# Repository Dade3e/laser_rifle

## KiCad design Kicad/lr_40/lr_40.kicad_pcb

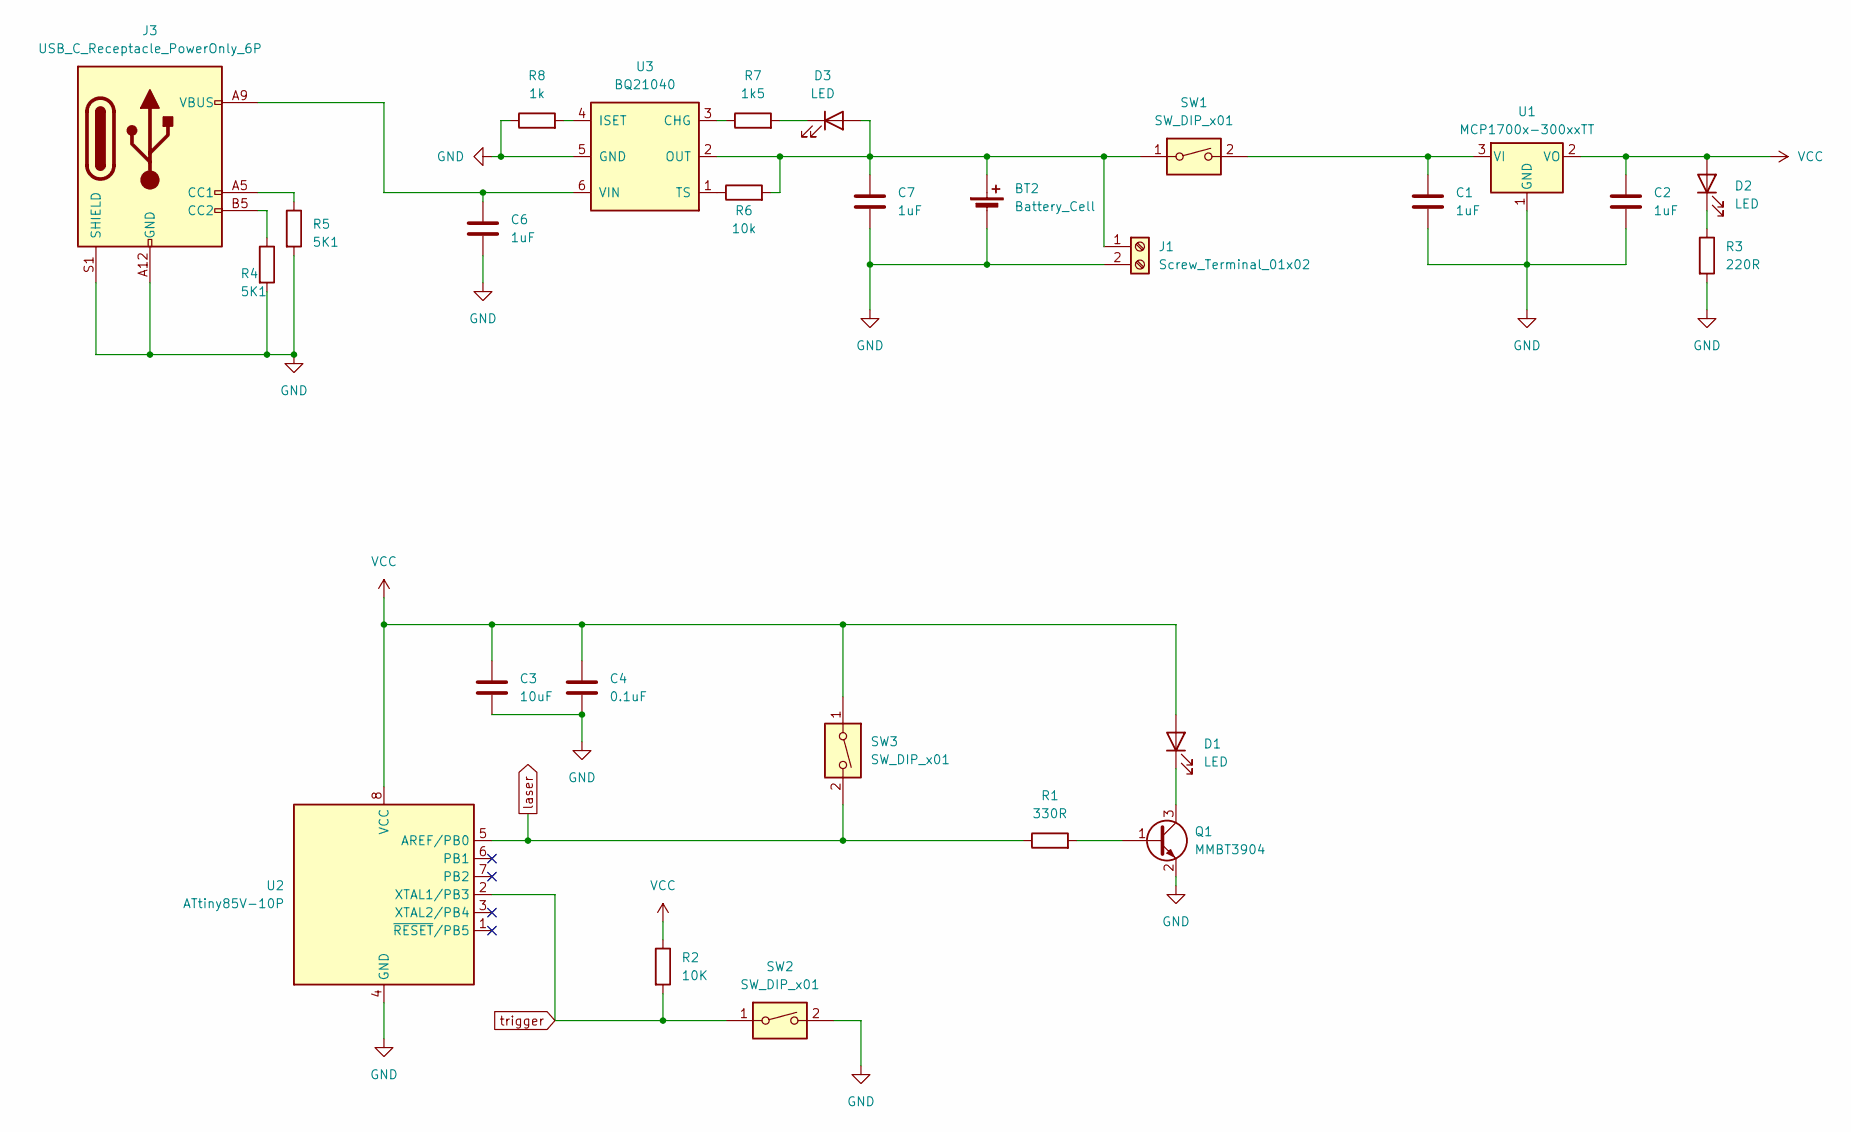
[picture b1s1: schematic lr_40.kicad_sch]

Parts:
BT2: Battery_Cell; Hirose_DF13C_CL535-0402-2-51_1x02-1MP_P1.25mm_Vertical
C1, C2, C6, C7: 1uF; C_0603_1608Metric
C3: 10uF; R_0603_1608Metric
C4: 0.1uF; R_0603_1608Metric
D1: LED; PinSocket_1x02_P2.54mm_Vertical
D2, D3: LED; LED_0603_1608Metric
J1: Screw_Terminal_01x02; PinSocket_1x02_P2.54mm_Vertical
J3: USB_C_Receptacle_PowerOnly_6P; USB_C_Receptacle_GCT_USB4115-03-C
Q1: MMBT3904; SOT-23
R1: 330R; R_0603_1608Metric
R2: 10K; R_0603_1608Metric
R3: 220R; R_0603_1608Metric
R4, R5: 5K1; R_0603_1608Metric
R6: 10k; R_0603_1608Metric
R7: 1k5; R_0603_1608Metric
R8: 1k; R_0603_1608Metric
SW1: SW_DIP_x01; SW_Slide_SPDT_Straight_CK_OS102011MS2Q
SW2: SW_DIP_x01; PinSocket_1x02_P2.54mm_Vertical
SW3: SW_DIP_x01; PinSocket_1x03_P2.54mm_Vertical
U1: MCP1700x-300xxTT; SOT-23
U2: ATtiny85V-10P; DIP-8_W7.62mm
U3: BQ21040; SOT-23-6_Handsoldering

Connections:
GND: BT2.2 (-), C1.2, C2.2, C3.2, C4.2, C6.2, C7.2, J1.2, J3.A12 (GND), J3.B12 (GND), J3.S1 (SHIELD), Q1.2 (E), R3.2, R4.2, R5.2, R8.1, SW2.2, U1.1 (GND), U2.4 (GND), U3.5 (GND)
unnamed: BT2.1 (+), C7.1, D3.2 (A), J1.1, R6.2, SW1.1, U3.2 (OUT)
unnamed: D1.1 (K), Q1.3 (C)
unnamed: D2.1 (K), R3.1
unnamed: D3.1 (K), R7.2
unnamed: J3.A5 (CC1), R5.1
unnamed: J3.B5 (CC2), R4.1
unnamed: Q1.1 (B), R1.2
unnamed: C1.1, SW1.2, U1.3 (VI)
unnamed: R7.1, U3.3 (CHG)
unnamed: R8.2, U3.4 (ISET)
unnamed: R6.1, U3.1 (TS)
unnamed: C6.1, J3.A9 (VBUS), J3.B9 (VBUS), U3.6 (VIN)
VCC: C2.1, C3.1, C4.1, D1.2 (A), D2.2 (A), R2.1, SW3.1, U1.2 (VO), U2.8 (VCC)
laser: R1.1, SW3.2, U2.5 (AREF/PB0)
trigger: R2.2, SW2.1, U2.2 (XTAL1/PB3)

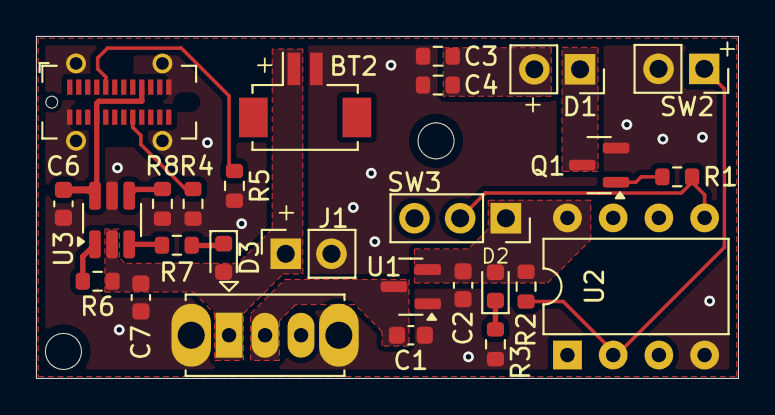
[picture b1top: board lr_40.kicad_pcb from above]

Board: 2 copper layers, 39.0 x 19.0 mm, 27 parts (0 on the bottom side), 16 nets.

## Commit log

2024-02-21 Primo commit
2024-02-21 Diviso il progetto dal bersaglio
2024-02-21 esport step
2024-02-28 Programma per scheda shot attiny
2024-02-28 Aggiunto delay debouncing
2024-02-28 Aggiunta variabile theshold
2024-02-28 cambiata soglia
2024-02-29 inserita la media dei max
2024-03-01 Corretti bugs
2024-04-17 PCB kicad
2024-04-18 Aggiornata pcb e creata pcb 48mm
2024-04-24 Nuova versione pcb
2025-06-26 Aggiunto grilletto con tolleranze stampa 3d
2025-06-30 update estetica e inizio laser
2025-07-02 Aggiunto fissaggio laser
2025-07-02 migliorato calcio
2025-07-03 Aggiunte versioni calcio
2025-07-03 Aggiunti nuovi calci e imgs
